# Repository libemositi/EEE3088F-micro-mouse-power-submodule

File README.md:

#Project Title: Micro-mouse Power Submodule

Description:
The Micro-mouse Power Submodule is a critical component of the Micro-mouse project, responsible for regulating voltage and providing power to the motors. This repository contains the KiCad design files, code, and documentation related to the Power Submodule.

Features:
Voltage regulation for motor control
Unit testing for individual components
User acceptance testing for usability
Business acceptance testing for alignment with project goals
Compliance testing for safety and standards
Alpha and beta testing for bug identification and user feedback
Installation:
Clone the repository:

git clone https://github.com/libemositi/micro-mouse-power-submodule.git
Install KiCad:

Download and install KiCad from KiCad Website
Usage:
Open KiCad and load the project files from the repository.
Review the schematic and PCB layout for the Power Submodule.
Make any necessary modifications or updates to the design.
Generate Gerber files for manufacturing.
Contributing:
Fork the repository
Create a new branch (git checkout -b feature)
Make changes and commit them (git commit -am 'Add new feature')
Push to the branch (git push origin feature)
Create a new Pull Request
License:
This project is licensed under the MIT License - see the LICENSE file for details.

Acknowledgements:
For any inquiries or support, please contact Libe at libemositi30110@gmail.com.

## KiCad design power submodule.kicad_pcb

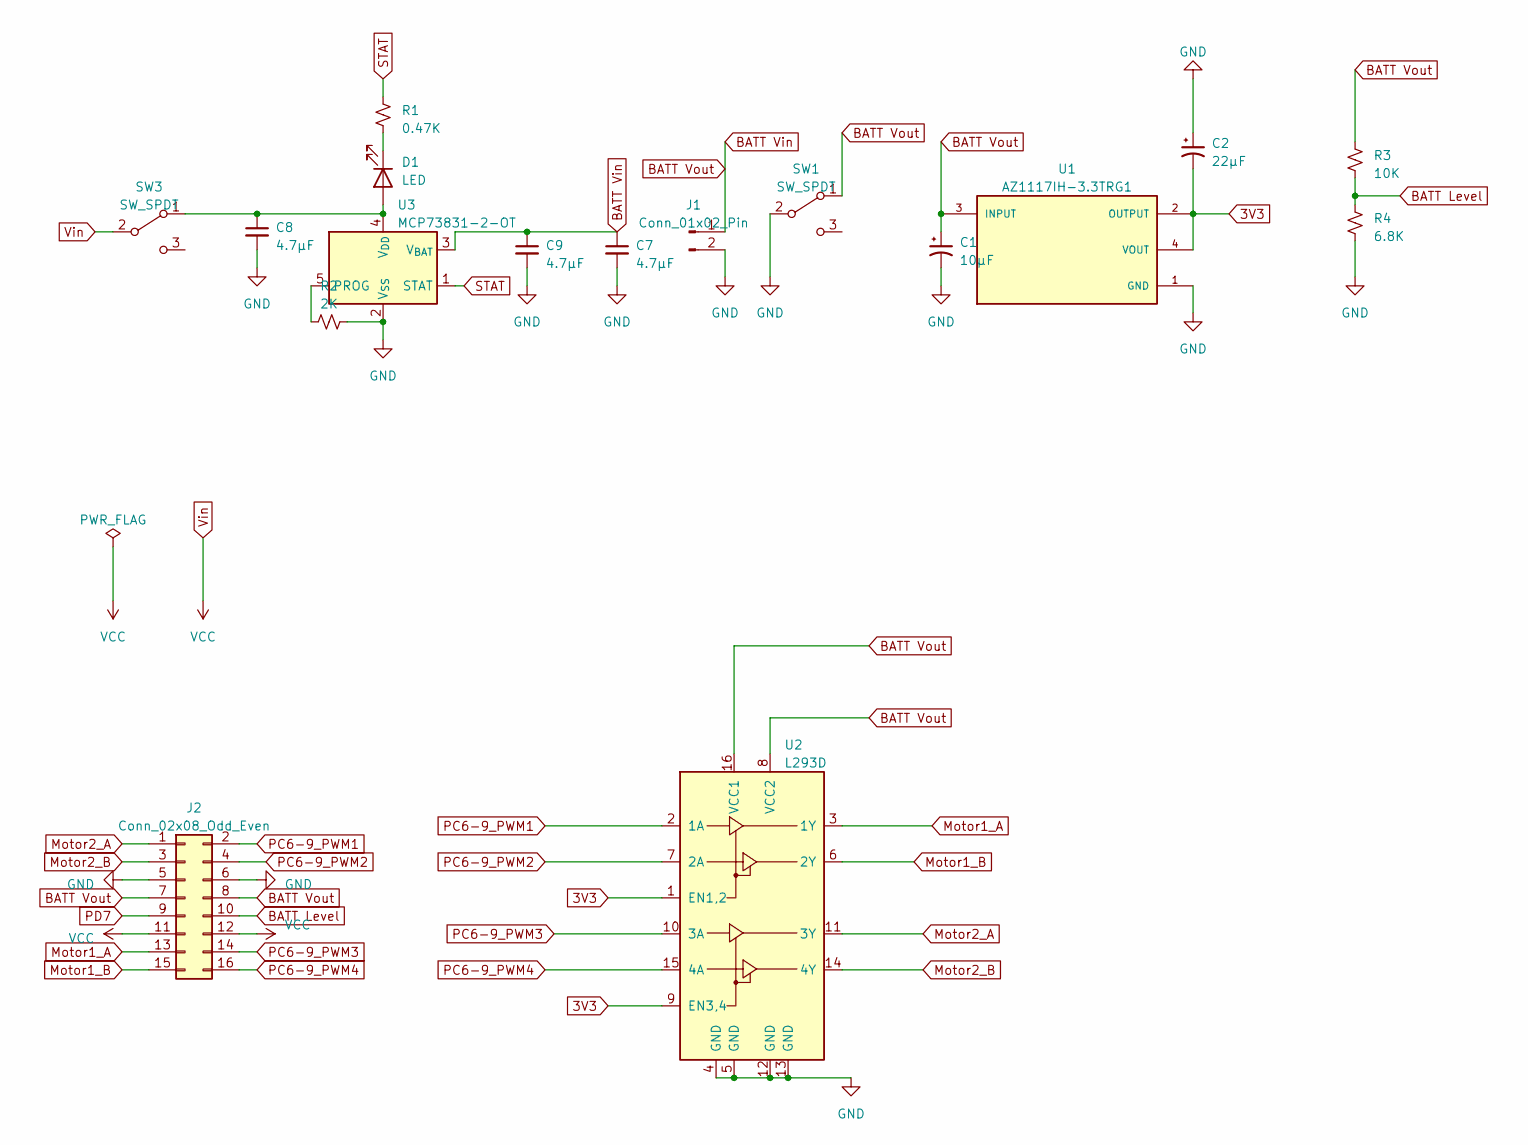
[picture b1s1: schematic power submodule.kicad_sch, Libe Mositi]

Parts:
C1: 10µF; C_0805_2012Metric_Pad1.18x1.45mm_HandSolder
C2: 22µF; C_0805_2012Metric_Pad1.18x1.45mm_HandSolder
C7, C8, C9: 4.7µF; C_0805_2012Metric_Pad1.18x1.45mm_HandSolder
D1: LED; LED_0805_2012Metric_Pad1.15x1.40mm_HandSolder
J1: Conn_01x02_Pin; JST_PH_B2B-PH-K_1x02_P2.00mm_Vertical
J2: Conn_02x08_Odd_Even; PinHeader_2x08_P2.54mm_Vertical
R1: 0.47K; R_0805_2012Metric_Pad1.20x1.40mm_HandSolder
R2: 2K; R_0805_2012Metric_Pad1.20x1.40mm_HandSolder
R3: 10K; R_0805_2012Metric_Pad1.20x1.40mm_HandSolder
R4: 6.8K; R_0805_2012Metric_Pad1.20x1.40mm_HandSolder
SW1, SW3: SW_SPDT; mySwitch
U1: AZ1117IH-3.3TRG1; SOT230P700X185-4N; PARTREV 2-2
U2: L293D; DIP-16_W7.62mm
U3: MCP73831-2-OT; SOT-23-5

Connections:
3V3: C2.2, U1.2 (OUTPUT), U1.4 (VOUT), U2.1 (EN1,2), U2.9 (EN3,4)
BATT Level: J2.10, R3.1, R4.1
BATT Vin: C1.1, C7.1, C9.1, J1.1, J2.7, J2.8, R3.2, SW1.1 (A), U1.3 (INPUT), U2.8 (VCC2), U2.16 (VCC1), U3.3 (V_{BAT})
GND: C1.2, C2.1, C7.2, C8.2, C9.2, J1.2, J2.5, J2.6, R2.2, R4.2, SW1.2 (B), U1.1 (GND), U2.4 (GND), U2.5 (GND), U2.12 (GND), U2.13 (GND), U3.2 (V_{SS})
Motor1_A: J2.13, U2.3 (1Y)
Motor1_B: J2.15, U2.6 (2Y)
Motor2_A: J2.1, U2.11 (3Y)
Motor2_B: J2.3, U2.14 (4Y)
unnamed: C8.1, D1.2 (A), SW3.1 (A), U3.4 (V_{DD})
unnamed: D1.1 (K), R1.2
unnamed: R2.1, U3.5 (PROG)
PC6-9_PWM1: J2.2, U2.2 (1A)
PC6-9_PWM2: J2.4, U2.7 (2A)
PC6-9_PWM3: J2.14, U2.10 (3A)
PC6-9_PWM4: J2.16, U2.15 (4A)
PD7: J2.9
STAT: R1.1, U3.1 (STAT)
Vin: J2.11, J2.12, SW3.2 (B)

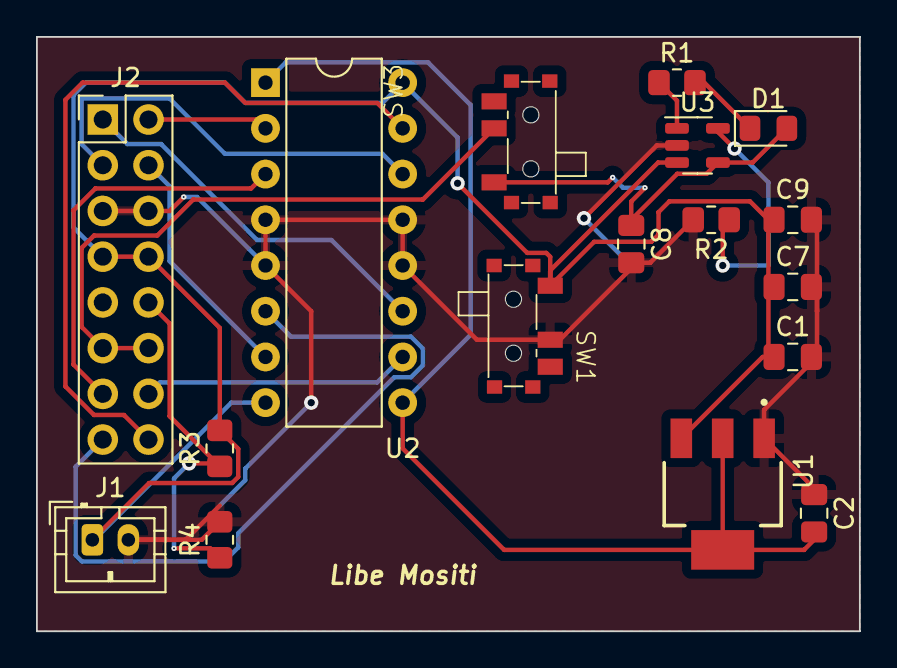
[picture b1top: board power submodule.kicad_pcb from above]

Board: 2 copper layers, 45.7 x 33.0 mm, 17 parts (0 on the bottom side), 17 nets.

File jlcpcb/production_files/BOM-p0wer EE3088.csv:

Comment,Designator,Footprint,LCSC
AZ1117IH-3.3TRG1,U1,SOT230P700X185-4N,C108495
MCP73831-2-OT,U3,SOT-23-5,C14879
10µF,C1,C_0805_2012Metric_Pad1.18x1.45mm_HandSolder,C15850
2K,R2,R_0805_2012Metric_Pad1.20x1.40mm_HandSolder,C17379
10K,R3,R_0805_2012Metric_Pad1.20x1.40mm_HandSolder,C17414
6.8K,R4,R_0805_2012Metric_Pad1.20x1.40mm_HandSolder,C17772
4.7µF,"C7,C8,C9",C_0805_2012Metric_Pad1.18x1.45mm_HandSolder,C1779
SW_SPDT,"SW1,SW3",mySwitch,C2890358
LED,D1,LED_0805_2012Metric_Pad1.15x1.40mm_HandSolder,C34499
0.47K,R1,R_0805_2012Metric_Pad1.20x1.40mm_HandSolder,C4310
L293D,U2,DIP-16_W7.62mm,C434590
22µF,C2,C_0805_2012Metric_Pad1.18x1.45mm_HandSolder,C45783
